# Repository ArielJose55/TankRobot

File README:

Proyecto que consiste en un robot tipo tanque oruga controlado desde una app android, por medio que interfaz Bluetooth del smartphone y un modulo bluetooth HC-06 que envía los datos por un puerto serial a arduino, este los procesa y gestiona el movimiento del tanque.

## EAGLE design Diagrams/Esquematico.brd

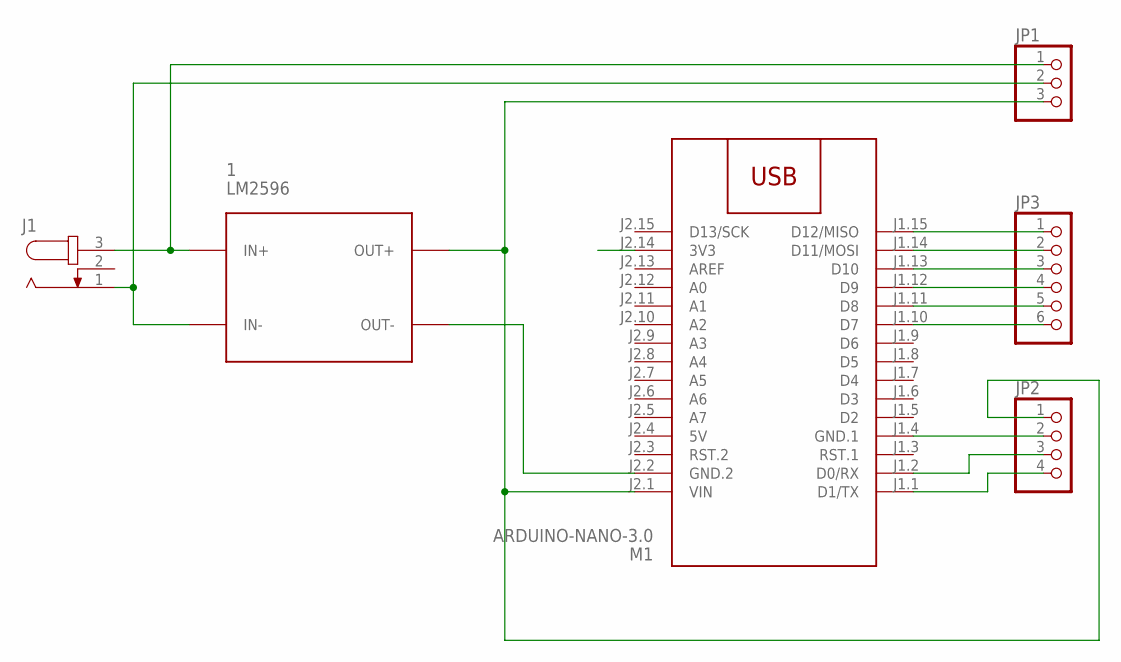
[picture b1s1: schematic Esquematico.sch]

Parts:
1: LM2596; DC-DC-STEP-DOWN-LM2596
J1: JACK-PLUG0; SPC4077
JP1: PINHD-1X3; 1X03
JP2: PINHD-1X4; 1X04
JP3: PINHD-1X6; 1X06
M1: ARDUINO-NANO-3.0

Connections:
5V: M1.J2.4 (5V)
unnamed: 1.IN-, J1.1, JP1.2
unnamed: 1.OUT+, JP1.3, JP2.1, M1.J2.1 (VIN)
unnamed: JP3.1, M1.J1.15 (D12/MISO)
unnamed: JP3.2, M1.J1.14 (D11/MOSI)
unnamed: JP3.3, M1.J1.13 (D10)
unnamed: JP3.4, M1.J1.12 (D9)
unnamed: JP3.5, M1.J1.11 (D8)
unnamed: JP3.6, M1.J1.10 (D7)
unnamed: JP2.2, M1.J1.4 (GND.1)
unnamed: JP2.4, M1.J1.1 (D1/TX)
unnamed: JP2.3, M1.J1.2 (D0/RX)
unnamed: 1.OUT-, M1.J2.2 (GND.2)
unnamed: 1.IN+, J1.3, JP1.1

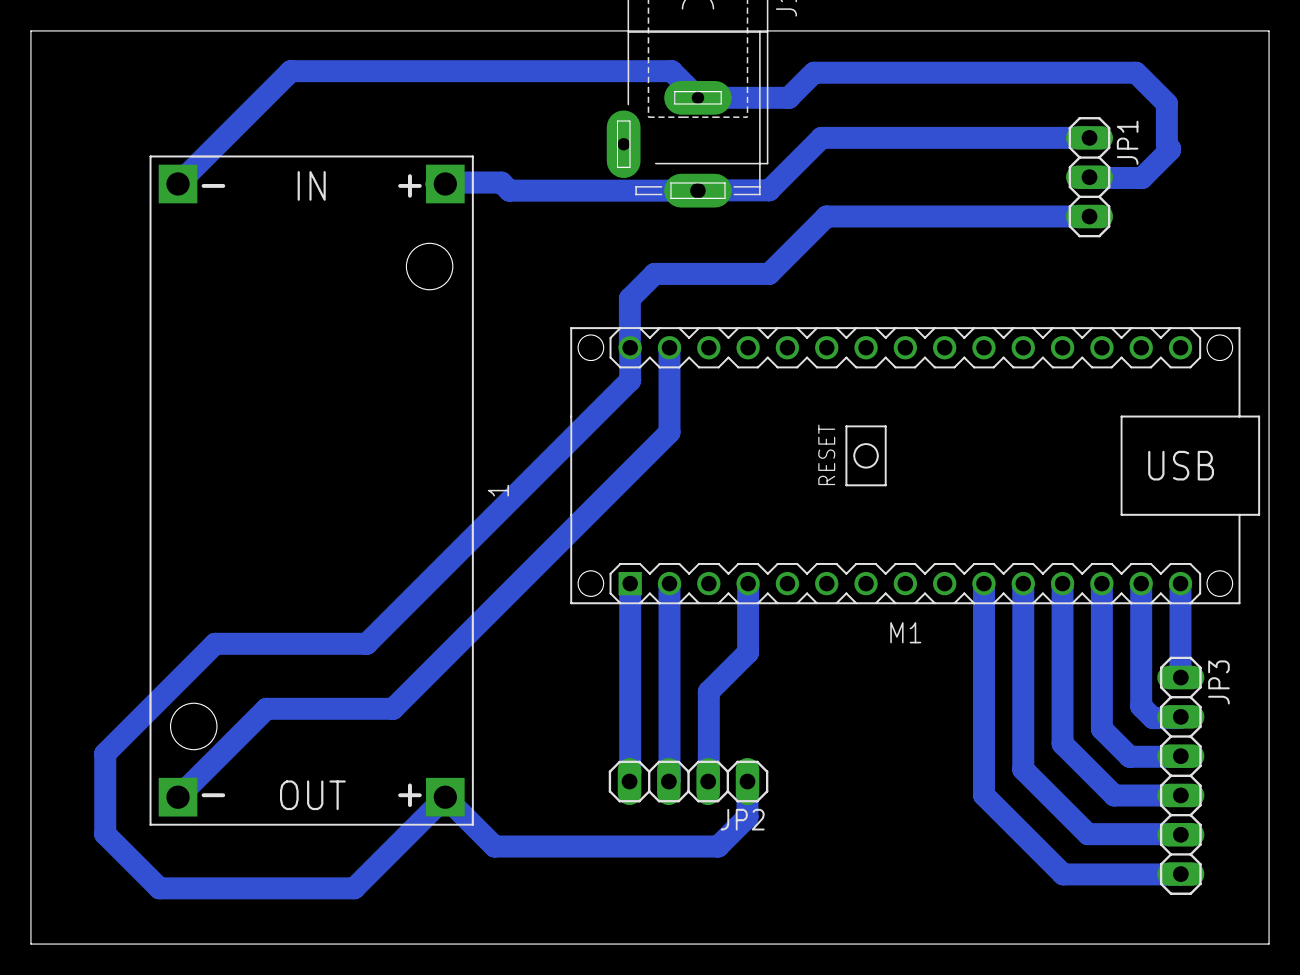
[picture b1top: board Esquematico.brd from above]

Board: 2 copper layers, 80.0 x 59.0 mm, 6 parts (0 on the bottom side), 13 nets.

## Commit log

2018-05-12 add the folders

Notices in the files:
parts and their libraries:
diy-modules: Released under the Creative Commons Attribution 4.0 International License: http://creativecommons.org/licenses/by/4.0
